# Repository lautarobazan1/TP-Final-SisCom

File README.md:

# BME280 y batería por LoRa

Primera etapa: **LoRa Radio Node v1.0 (ATmega328P) → Heltec Wireless Tracker (ESP32-S3 + SX1262)**. La Tracker muestra temperatura, humedad, presión y la batería **del nodo remoto**.

Anteproyecto de hardware: [PCB integradora, gabinete y cabezal de medición](hardware/ANTEPROYECTO.md). Incluye archivos KiCad y FreeCAD provisionales; faltan medidas físicas, selección de gabinete y ruteo.

Los programas parten de `Radio Node.txt` y `Heltec Wireless Tracker.txt`. Los dos originales se conservan. Se mantienen sus pines, la inicialización TFT y los parámetros del enlace: **915 MHz, SF7, BW 125 kHz, CR 4/5, sync word 0x12**, potencia de 14 dBm y preámbulo de 8 símbolos. Se habilitó CRC en ambos extremos.

## Archivos para cargar

- `firmware/LoRaNodeV1/LoRaNodeV1.ino`: lee el BME280 y transmite cada 5 segundos.
- `firmware/HeltecWirelessTracker/HeltecWirelessTracker.ino`: recibe y muestra los datos en la TFT ST7735 de 160×80.
- Cada carpeta contiene `Config.h` y `Telemetria.h`; conservarlos junto a su `.ino`. Arduino IDE los abre como pestañas. Las dos copias de `Telemetria.h` deben mantenerse idénticas.

## Conexión del BME280 al nodo

| BME280 | LoRa Radio Node v1.0 |
| --- | --- |
| VCC/VIN | 3V3 |
| GND | GND |
| SDA | A4 / SDA |
| SCL | A5 / SCL |

Se prueban automáticamente las direcciones `0x76` y `0x77`. En módulos con CS/CSB y SDO expuestos, CS debe quedar alto para I2C y SDO determina la dirección; seguir el pinout de tu módulo. Un **BMP280** no mide humedad y este código requiere **BME280**.

## Conexión y configuración de la batería

El `Config.h` actual tiene `BATTERY_CONNECTED = true`, resistencias de **150 kΩ + 150 kΩ** y `ADC_REFERENCE_MV = 3226`. Esto describe la configuración del firmware; hay que verificar que coincida con el divisor y la alimentación físicos. Si el divisor no está montado, poner `BATTERY_CONNECTED = false`; la pantalla mostrará **`Bat: -- (sin medicion)`**.

Para una **Li-ion de una celda, nominal 3,7 V, máximo 4,2 V**, conectar:

```text
BAT+ antes del regulador --- R1 150 kohm ---+--- R2 150 kohm --- GND
                                          |
                                          +--- A0 del nodo
                                          |
                                          +--- C1 100 nF ----- GND

BAT- ------------------------------------------ GND del nodo
```

1. Montar el divisor y compartir GND. C1 ayuda a estabilizar la entrada por el valor alto de las resistencias. Esperar al menos 50 ms desde la alimentación antes de medir; el arranque del programa ya supera ese tiempo.
2. Verificar con multímetro que A0 esté aproximadamente a **la mitad de la tensión de batería**: 2,10 V si la batería está a 4,20 V. **No conectar BAT+ directamente a A0**.
3. En `firmware/LoRaNodeV1/Config.h`, dejar `BATTERY_CONNECTED = true` solamente si el divisor está montado y comprobado. Cargar el nodo después de cualquier cambio.
4. Medir 3V3 respecto de GND y ajustar `ADC_REFERENCE_MV` a ese valor en milivoltios. La referencia del ADC es VCC, no la tensión nominal de la batería. Si queda una diferencia con el multímetro, ajustar `BATTERY_CALIBRATION = tension_real / tension_mostrada` partiendo de 1,0.

El código promedia 32 muestras antes de transmitir. La fórmula es `VBAT = ADC × VREF / 1023 × (R1 + R2) / R2`. Recalibrar si cambia la alimentación de 3V3. Cuando la batería baja tanto que el regulador pierde regulación, VCC deja de ser constante y la lectura requiere corregir la referencia.

La pantalla muestra voltios y **porcentaje aproximado** (`~`) mediante una curva orientativa para Li-ion de una celda. No equivale a medir capacidad restante y no sustituye la protección de la batería. El divisor de 150 kΩ + 150 kΩ toma unos 14 µA a 4,2 V. Esta etapa no implementa sueño del ATmega ni demuestra todavía la autonomía del proyecto.

## Carga en Arduino IDE

Bibliotecas del Gestor de bibliotecas:

| Placa | Bibliotecas |
| --- | --- |
| Nodo | **LoRa** de Sandeep Mistry; **Adafruit BME280 Library** y sus dependencias **Adafruit Unified Sensor** y **Adafruit BusIO** |
| Tracker | **RadioLib** de Jan Gromes; **Adafruit GFX Library**; **Adafruit ST7735 and ST7789 Library**, con sus dependencias |

1. Abrir `LoRaNodeV1.ino`. Seleccionar **Arduino Pro or Pro Mini → ATmega328P (3.3V, 8 MHz)**. Usar un adaptador USB-serie con **lógica de 3,3 V** según el pinout de la placa. Monitor serie: **9600 baud**. No seleccionar la variante de 16 MHz.
2. Abrir `HeltecWirelessTracker.ino`. Seleccionar **Heltec Wireless Tracker**, usando el paquete ESP32 que ya tenés instalado. Monitor serie: **115200 baud**. Mantener las opciones de carga/USB que ya funcionaban con tu ejemplo.
3. Conectar las antenas de 915 MHz antes de encender y cargar los dos programas. El nuevo formato de datos requiere ambos firmwares; el receptor nuevo descarta el antiguo mensaje `Hola Heltec!`.

## Qué debe verse

```text
BME280 + BATERIA NODO
Nodo 1  RSSI -72 dBm
Temp: 23.45 C
Hum:  56.78 %
Pres: 1013.2 hPa
Bat: 3.85 V ~50%
Edad 0s  #12
```

Los números anteriores son solo un ejemplo. Sin divisor, la fila de batería indica que no hay medición. Al arrancar la Tracker espera el primer paquete. Si pasan **20 segundos sin un paquete válido del nodo 1**, muestra **`SIN DATOS RECIENTES`** y conserva los últimos valores en amarillo, con su antigüedad. Si el nodo informa un fallo del BME280, muestra el error sin inventar lecturas; el nodo reintenta detectar el sensor en el siguiente ciclo.

Para probar: comprobar cambios del sensor, desconectar el BME280 y comprobar el mensaje de error, apagar el nodo durante más de 20 segundos y comprobar el estado de datos antiguos, luego reconectarlo y comprobar recuperación. Después de montar el divisor, comparar batería con multímetro. No desconectar cables de alimentación provocando cortocircuitos.

## Formato del paquete

19 bytes, enteros little-endian; no se transmite directamente una estructura C ni valores `float`.

| Bytes | Contenido |
| --- | --- |
| 0–2 | `S`, `C`, versión `1` |
| 3 | ID de nodo, inicialmente `1` |
| 4 | bit 0: BME280 válido; bit 1: batería válida |
| 5–8 | contador de envíos (`uint32_t`, reinicia al arrancar) |
| 9–10 | temperatura en centésimas de °C (`int16_t`) |
| 11–12 | humedad en centésimas de % (`uint16_t`) |
| 13–16 | presión en Pa (`uint32_t`) |
| 17–18 | batería en mV (`uint16_t`) |

Los campos cuya bandera no está activa no se muestran como mediciones. La Tracker valida longitud, identificador, versión, banderas, ID del nodo y rangos; la radio comprueba el CRC LoRa. Es un enlace local de un solo nodo, sin confirmación de entrega ni cifrado.

## Verificación y referencias

Las versiones locales usadas para compilar se registran en `VALIDACION.md`. `tests/telemetria_test.cpp` comprueba bytes conocidos, temperaturas negativas, extremos y rechazo de paquetes inválidos. La compilación no sustituye la prueba con las placas físicas.

- [LoRa Radio Node v1.0: esquema del fabricante IOT-MCU](https://github.com/IOT-MCU/LoRa-Radio-Node-v1.0). Confirma SPI D10/D9/D2, I2C A4/A5 y reloj de 8 MHz; este esquema no incluye un divisor de batería al ADC.
- [Heltec Wireless Tracker](https://heltec.org/project/wireless-tracker/): modelo ESP32-S3 + SX1262 y pantalla TFT.
- [API de Arduino LoRa](https://github.com/sandeepmistry/arduino-LoRa/blob/master/API.md) y [configuración de RadioLib](https://github.com/jgromes/RadioLib/wiki/Default-configuration).

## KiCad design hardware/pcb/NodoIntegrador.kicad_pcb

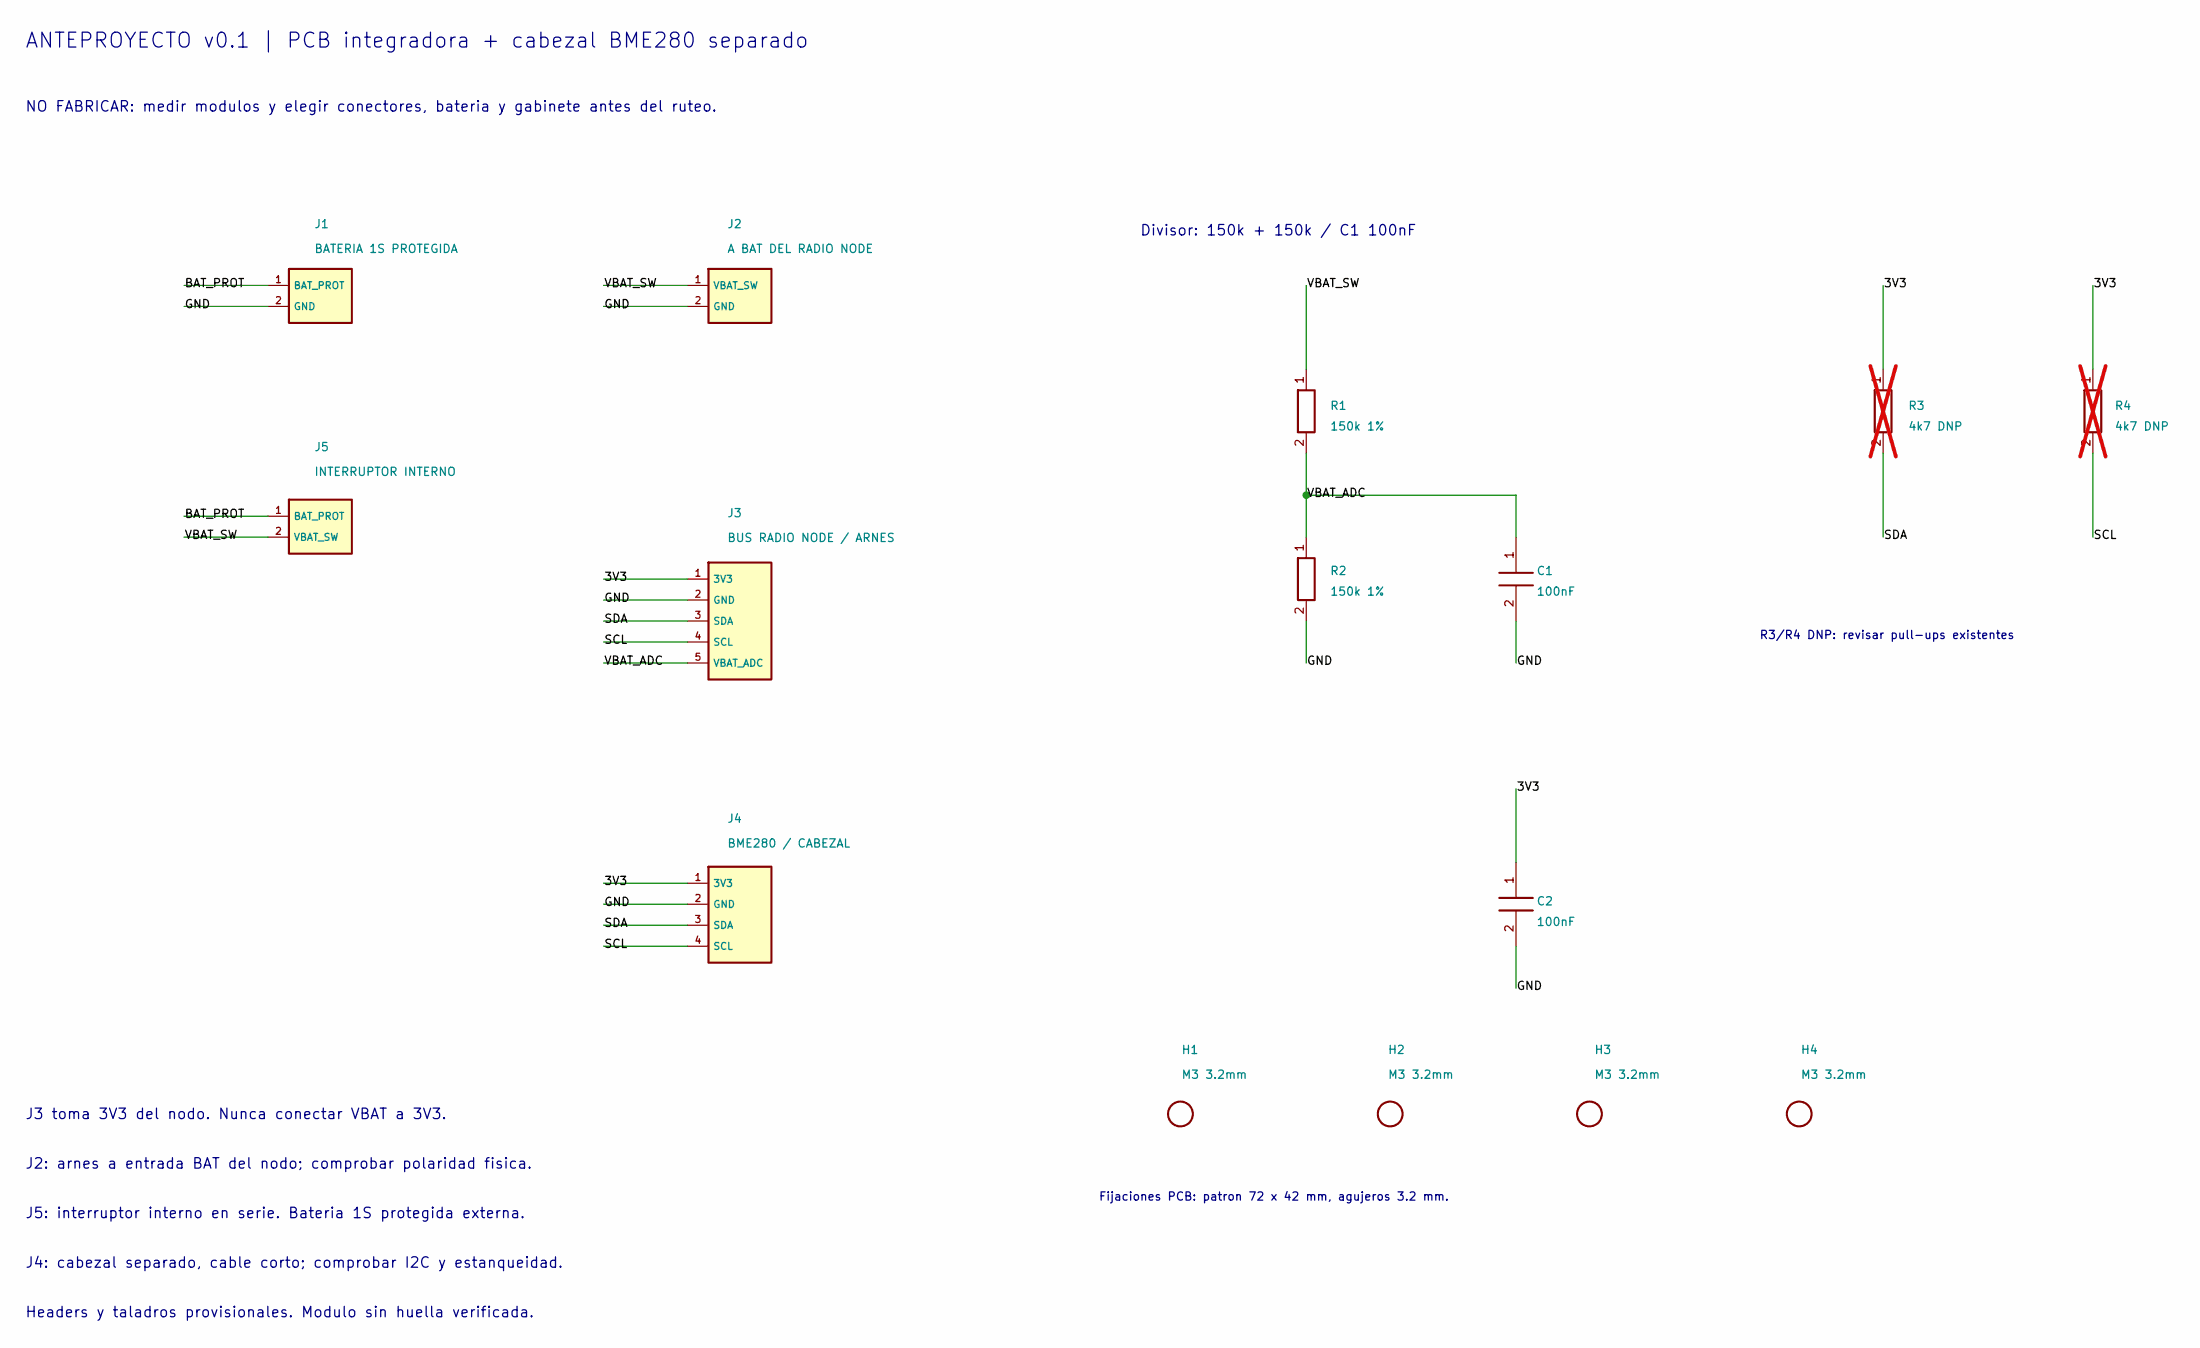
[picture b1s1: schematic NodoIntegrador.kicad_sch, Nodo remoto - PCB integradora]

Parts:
C1, C2: 100nF; C_0805_2012Metric
H1, H2, H3, H4: M3 3.2mm; MountingHole_3.2mm_M3
J1: BATERIA 1S PROTEGIDA; PinHeader_1x02_P2.54mm_Vertical
J2: A BAT DEL RADIO NODE; PinHeader_1x02_P2.54mm_Vertical
J3: BUS RADIO NODE / ARNES; PinHeader_1x05_P2.54mm_Vertical
J4: BME280 / CABEZAL; PinHeader_1x04_P2.54mm_Vertical
J5: INTERRUPTOR INTERNO; PinHeader_1x02_P2.54mm_Vertical
R1, R2: 150k 1%; R_0805_2012Metric
R3, R4: 4k7 DNP; R_0805_2012Metric; not fitted

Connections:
/3V3: C2.1, J3.1 (3V3), J4.1 (3V3), R3.1, R4.1
/BAT_PROT: J1.1 (BAT_PROT), J5.1 (BAT_PROT)
/GND: C1.2, C2.2, J1.2 (GND), J2.2 (GND), J3.2 (GND), J4.2 (GND), R2.2
/SCL: J3.4 (SCL), J4.4 (SCL), R4.2
/SDA: J3.3 (SDA), J4.3 (SDA), R3.2
/VBAT_ADC: C1.1, J3.5 (VBAT_ADC), R1.2, R2.1
/VBAT_SW: J2.1 (VBAT_SW), J5.2 (VBAT_SW), R1.1

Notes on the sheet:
ANTEPROYECTO v0.1 | PCB integradora + cabezal BME280 separado
NO FABRICAR: medir modulos y elegir conectores, bateria y gabinete antes del ruteo.
Divisor: 150k + 150k / C1 100nF
R3/R4 DNP: revisar pull-ups existentes
J3 toma 3V3 del nodo. Nunca conectar VBAT a 3V3.
J2: arnes a entrada BAT del nodo; comprobar polaridad fisica.
J5: interruptor interno en serie. Bateria 1S protegida externa.
J4: cabezal separado, cable corto; comprobar I2C y estanqueidad.
Headers y taladros provisionales. Modulo sin huella verificada.
Fijaciones PCB: patron 72 x 42 mm, agujeros 3.2 mm.

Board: 2 copper layers, 15 parts (0 on the bottom side), 7 nets, no tracks yet.

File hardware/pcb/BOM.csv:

Referencia,Valor_funcion,Huella_provisional,Montaje,Estado
J1,BATERIA 1S PROTEGIDA,Connector_PinHeader_2.54mm:PinHeader_1x02_P2.54mm_Vertical,PREVISTO,ANTEPROYECTO
J2,A BAT DEL RADIO NODE,Connector_PinHeader_2.54mm:PinHeader_1x02_P2.54mm_Vertical,PREVISTO,ANTEPROYECTO
J3,BUS RADIO NODE / ARNES,Connector_PinHeader_2.54mm:PinHeader_1x05_P2.54mm_Vertical,PREVISTO,ANTEPROYECTO
J4,BME280 / CABEZAL,Connector_PinHeader_2.54mm:PinHeader_1x04_P2.54mm_Vertical,PREVISTO,ANTEPROYECTO
J5,INTERRUPTOR INTERNO,Connector_PinHeader_2.54mm:PinHeader_1x02_P2.54mm_Vertical,PREVISTO,ANTEPROYECTO
R1,150k 1%,Resistor_SMD:R_0805_2012Metric,PREVISTO,ANTEPROYECTO
R2,150k 1%,Resistor_SMD:R_0805_2012Metric,PREVISTO,ANTEPROYECTO
C1,100nF,Capacitor_SMD:C_0805_2012Metric,PREVISTO,ANTEPROYECTO
C2,100nF,Capacitor_SMD:C_0805_2012Metric,PREVISTO,ANTEPROYECTO
R3,4k7 DNP,Resistor_SMD:R_0805_2012Metric,DNP,ANTEPROYECTO
R4,4k7 DNP,Resistor_SMD:R_0805_2012Metric,DNP,ANTEPROYECTO
H1,M3 3.2mm,MountingHole:MountingHole_3.2mm_M3,PREVISTO,ANTEPROYECTO
H2,M3 3.2mm,MountingHole:MountingHole_3.2mm_M3,PREVISTO,ANTEPROYECTO
H3,M3 3.2mm,MountingHole:MountingHole_3.2mm_M3,PREVISTO,ANTEPROYECTO
H4,M3 3.2mm,MountingHole:MountingHole_3.2mm_M3,PREVISTO,ANTEPROYECTO

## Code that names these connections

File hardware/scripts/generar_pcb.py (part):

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MFP = "MountingHole:MountingHole_3.2mm_M3"

components = [
    dict(ref="J1", kind="BAT_IN", value="BATERIA 1S PROTEGIDA", pins=["BAT_PROT", "GND"], sch=[50,45], pcb=[110,134], footprint=HEADER.format(n=2)),
    dict(ref="J2", kind="BAT_OUT", value="A BAT DEL RADIO NODE", pins=["VBAT_SW", "GND"], sch=[100,45], pcb=[134,134], footprint=HEADER.format(n=2)),
    dict(ref="J3", kind="NODE_BUS", value="BUS RADIO NODE / ARNES", pins=["3V3", "GND", "SDA", "SCL", "VBAT_ADC"], sch=[100,80], pcb=[155,110], footprint=HEADER.format(n=5)),
    dict(ref="J4", kind="SENSOR_BUS", value="BME280 / CABEZAL", pins=["3V3", "GND", "SDA", "SCL"], sch=[100,117], pcb=[169,128], footprint=HEADER.format(n=4)),
    dict(ref="J5", kind="SWITCH", value="INTERRUPTOR INTERNO", pins=["BAT_PROT", "VBAT_SW"], sch=[50,72], pcb=[122,134], footprint=HEADER.format(n=2)),
    dict(ref="R1", kind="R", value="150k 1%", pins=["VBAT_SW", "VBAT_ADC"], sch=[170,60], pcb=[148,133], footprint=RFP),
    dict(ref="R2", kind="R", value="150k 1%", pins=["VBAT_ADC", "GND"], sch=[170,80], pcb=[148,139], footprint=RFP),
    dict(ref="C1", kind="C", value="100nF", pins=["VBAT_ADC", "GND"], sch=[195,80], pcb=[155,139], footprint=CFP),
    dict(ref="C2", kind="C", value="100nF", pins=["3V3", "GND"], sch=[195,120], pcb=[163,139], footprint=CFP),
    dict(ref="R3", kind="R", value="4k7 DNP", pins=["3V3", "SDA"], sch=[240,60], pcb=[162,123], footprint=RFP, dnp=True),
    dict(ref="R4", kind="R", value="4k7 DNP", pins=["3V3", "SCL"], sch=[265,60], pcb=[162,128], footprint=RFP, dnp=True),
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            label(net,x-15.24,py)

# Divisor vertical y capacitor del ADC.
wire(170,45,170,54.92); label("VBAT_SW",170,45)
wire(170,65.08,170,70); wire(170,70,170,74.92)
wire(170,70,195,70); wire(195,70,195,74.92); label("VBAT_ADC",170,70)
s.append(f'(junction (at {grid(170)} {grid(70)}) (diameter 0) (color 0 0 0 0) (uuid {uid("junction/adc")}))')
wire(170,85.08,170,90); label("GND",170,90)
wire(195,85.08,195,90); label("GND",195,90)
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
